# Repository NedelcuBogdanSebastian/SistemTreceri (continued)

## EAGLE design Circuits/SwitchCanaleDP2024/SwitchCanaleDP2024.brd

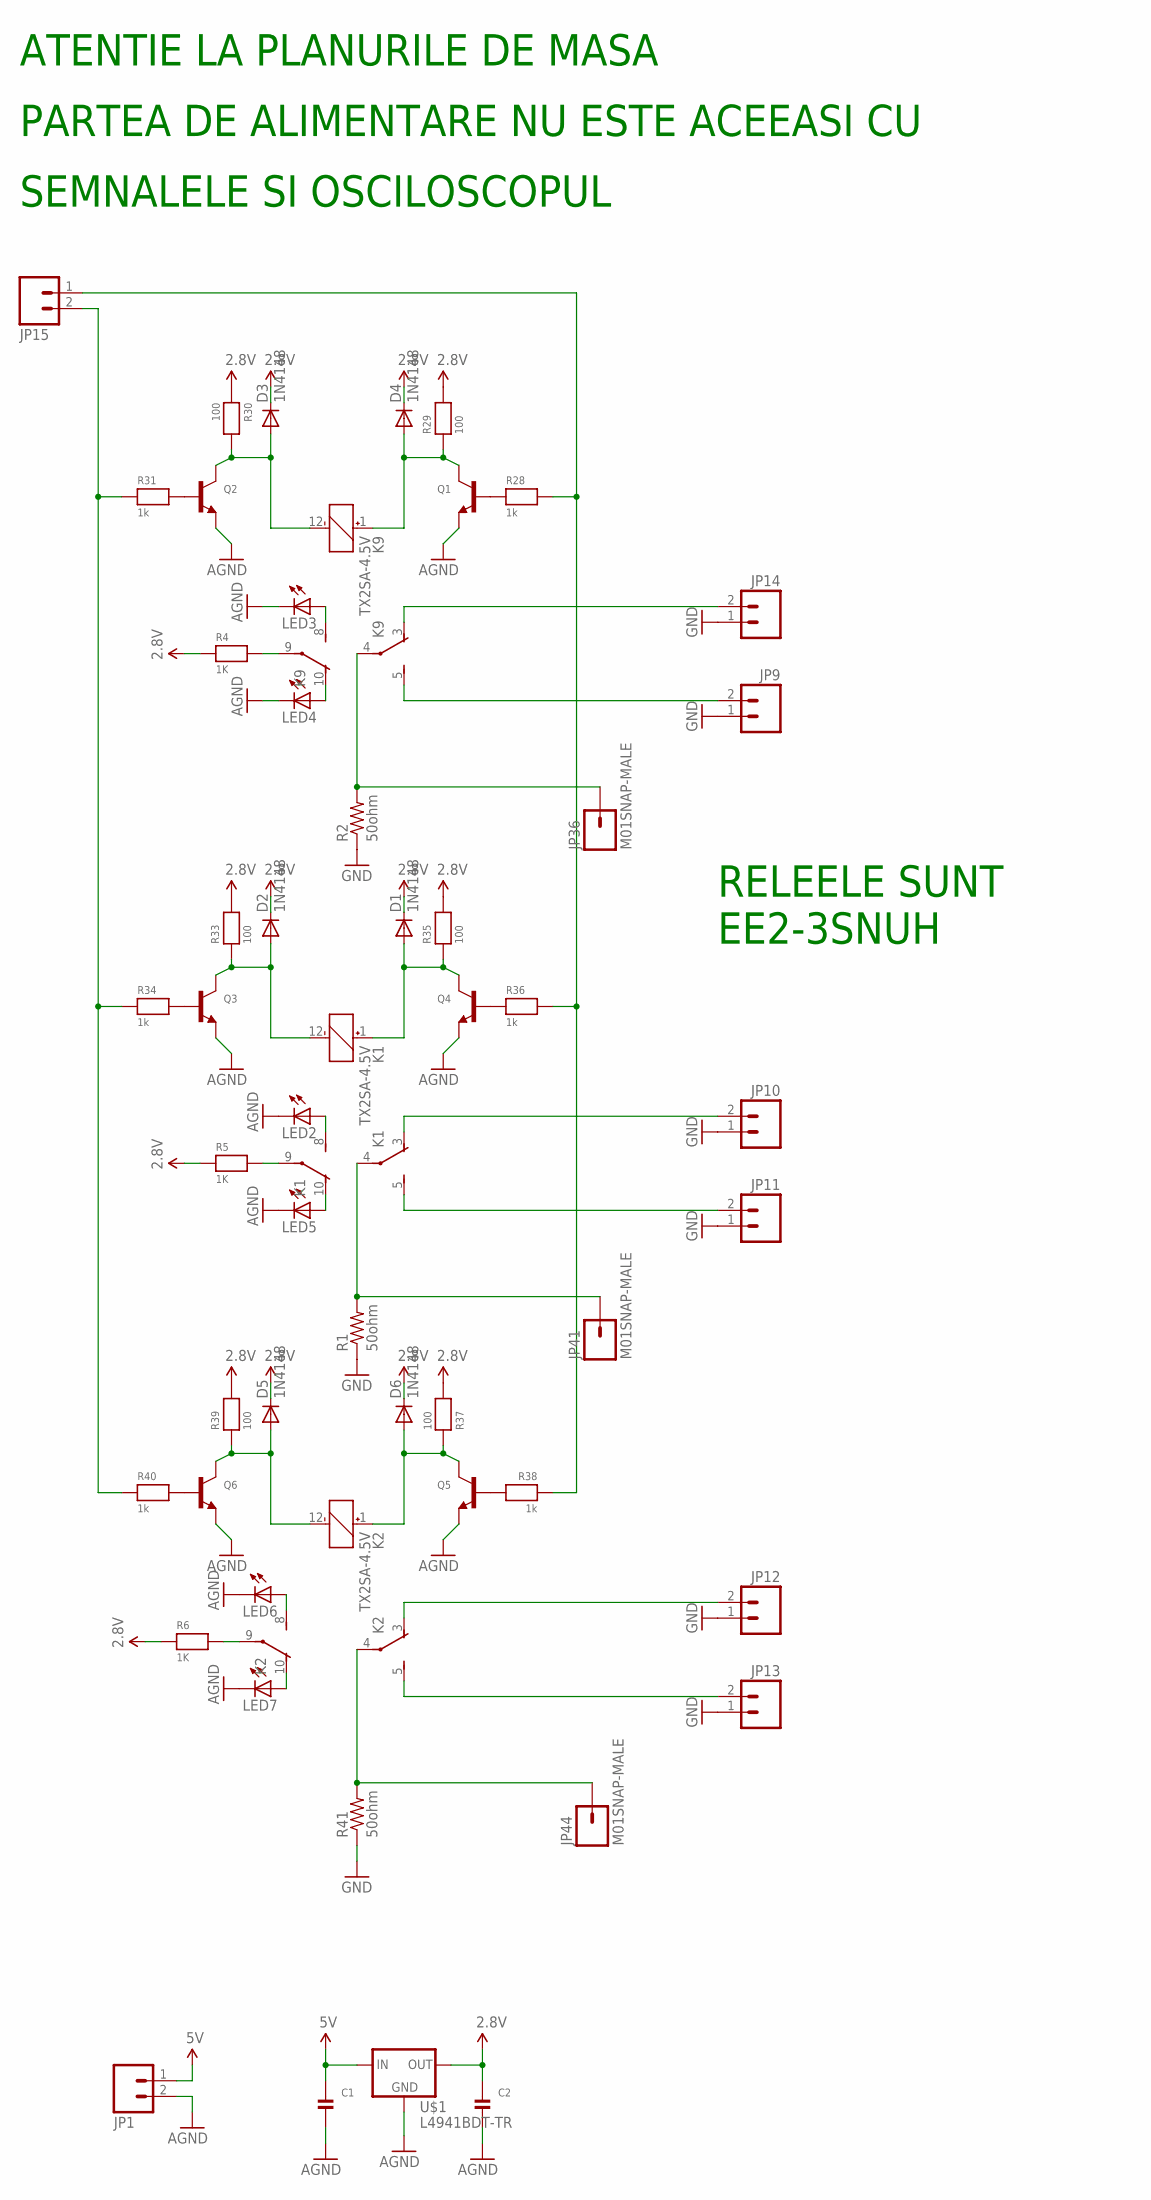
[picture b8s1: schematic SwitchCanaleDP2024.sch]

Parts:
C1, C2: CAP_CERAMIC1206; 1206
D1, D2, D3, D4, D5, D6: 1N4148; MINIMELF
JP1, JP9, JP10, JP11, JP12, JP13, JP14, JP15: M025MM; SCREWTERMINAL-5MM-2
JP36, JP41, JP44: M01SNAP-MALE; SNAP-MALE
K1, K2, K9: TX2SA-4.5V; TX2SA
LED2, LED3, LED4, LED5, LED6, LED7: LEDCHIP-LED0805; CHIP-LED0805
Q1, Q2, Q3, Q4, Q5, Q6: TRANSISTOR_NPNWAVE; SOT23-W
R1, R2, R41: 50ohm; 1206
R4, R5, R6: 1K; _0805MP
R28, R31, R34, R36, R38, R40: 1k; _0805MP
R29, R30, R33, R35, R37, R39: 100; _0805MP
U$1: L4941BDT-TR; DPAK

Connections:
2.8V: C2.1, D1.C, D2.C, D3.C, D4.C, D5.C, D6.C, R4.1, R5.1, R6.1, R29.2, R30.1, R33.2, R35.2, R37.2, R39.2, U$1.2 (OUT)
5V: C1.1, JP1.1, U$1.1 (IN)
AGND: C1.2, C2.2, JP1.2, LED2.C, LED3.C, LED4.C, LED5.C, LED6.C, LED7.C, Q1.2 (E), Q2.2 (E), Q3.2 (E), Q4.2 (E), Q5.2 (E), Q6.2 (E), U$1.3 (GND)
GND: JP9.1, JP10.1, JP11.1, JP12.1, JP13.1, JP14.1, R1.1, R2.1, R41.1
unnamed: JP15.2, R31.1, R34.1, R40.1
unnamed: D4.A, K9.1 (+), Q1.3 (C), R29.1
unnamed: K9.8 (S), LED3.A
unnamed: K9.10 (O), LED4.A
unnamed: K9.9, R4.2
unnamed: JP14.2, K9.3 (O)
unnamed: JP9.2, K9.5 (S)
unnamed: JP15.1, R28.2, R36.2, R38.1
unnamed: JP12.2, K2.3 (O)
unnamed: K1.8 (S), LED2.A
unnamed: K1.10 (O), LED5.A
unnamed: K2.8 (S), LED6.A
unnamed: K2.10 (O), LED7.A
unnamed: K2.9, R6.2
unnamed: JP36.2, K9.4, R2.2
unnamed: K1.9, R5.2
unnamed: D1.A, K1.1 (+), Q4.3 (C), R35.1
unnamed: D2.A, K1.12 (-), Q3.3 (C), R33.1
unnamed: JP10.2, K1.3 (O)
unnamed: JP11.2, K1.5 (S)
unnamed: JP41.2, K1.4, R1.2
unnamed: D6.A, K2.1 (+), Q5.3 (C), R37.1
unnamed: JP13.2, K2.5 (S)
unnamed: JP44.2, K2.4, R41.2
unnamed: Q5.1 (B), R38.2
unnamed: Q6.1 (B), R40.2
unnamed: D5.A, K2.12 (-), Q6.3 (C), R39.1
unnamed: D3.A, K9.12 (-), Q2.3 (C), R30.2
unnamed: Q2.1 (B), R31.2
unnamed: Q1.1 (B), R28.1
unnamed: Q3.1 (B), R34.2
unnamed: Q4.1 (B), R36.1

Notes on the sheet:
EE2-3SNUH
RELEELE SUNT
ATENTIE LA PLANURILE DE MASA
PARTEA DE ALIMENTARE NU ESTE ACEEASI CU
SEMNALELE SI OSCILOSCOPUL

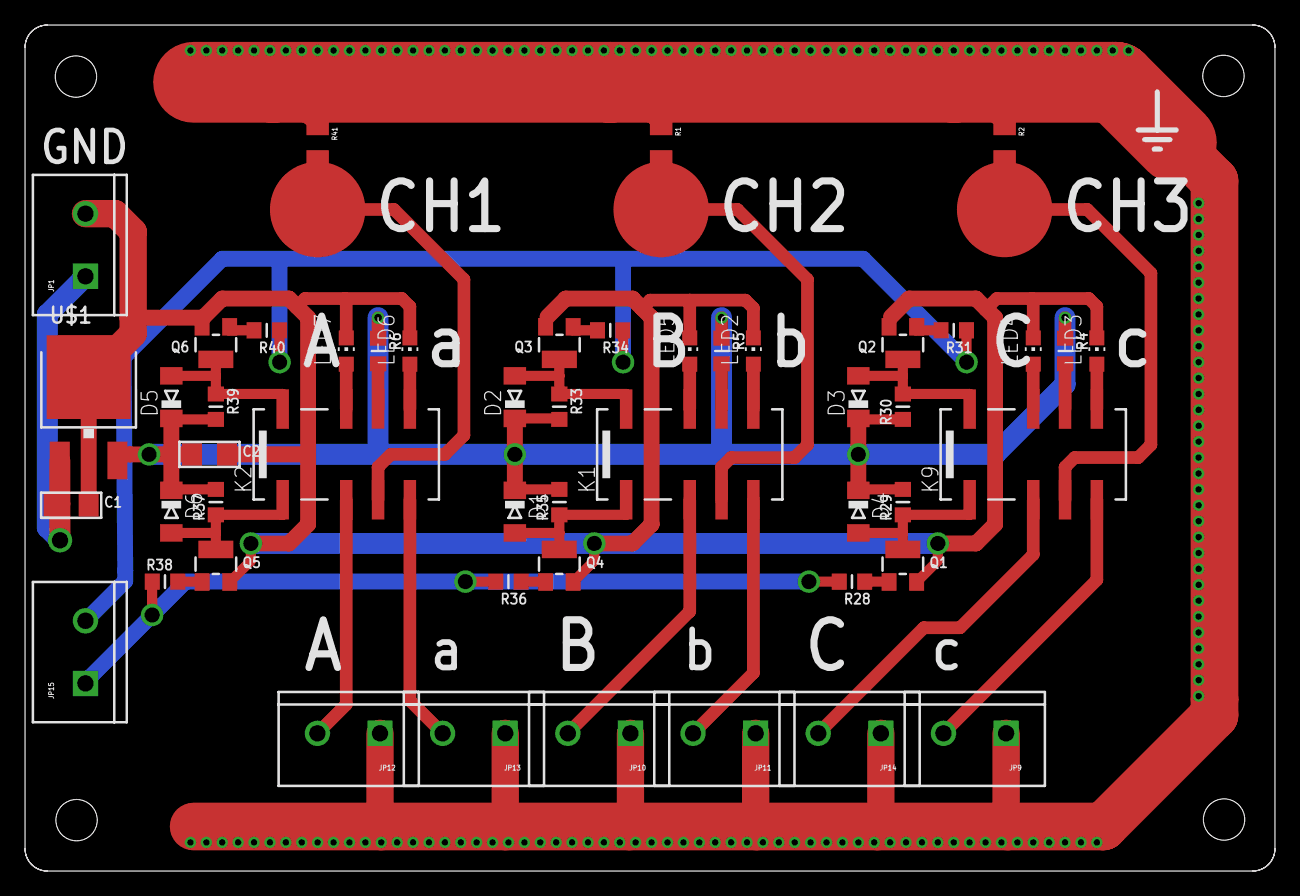
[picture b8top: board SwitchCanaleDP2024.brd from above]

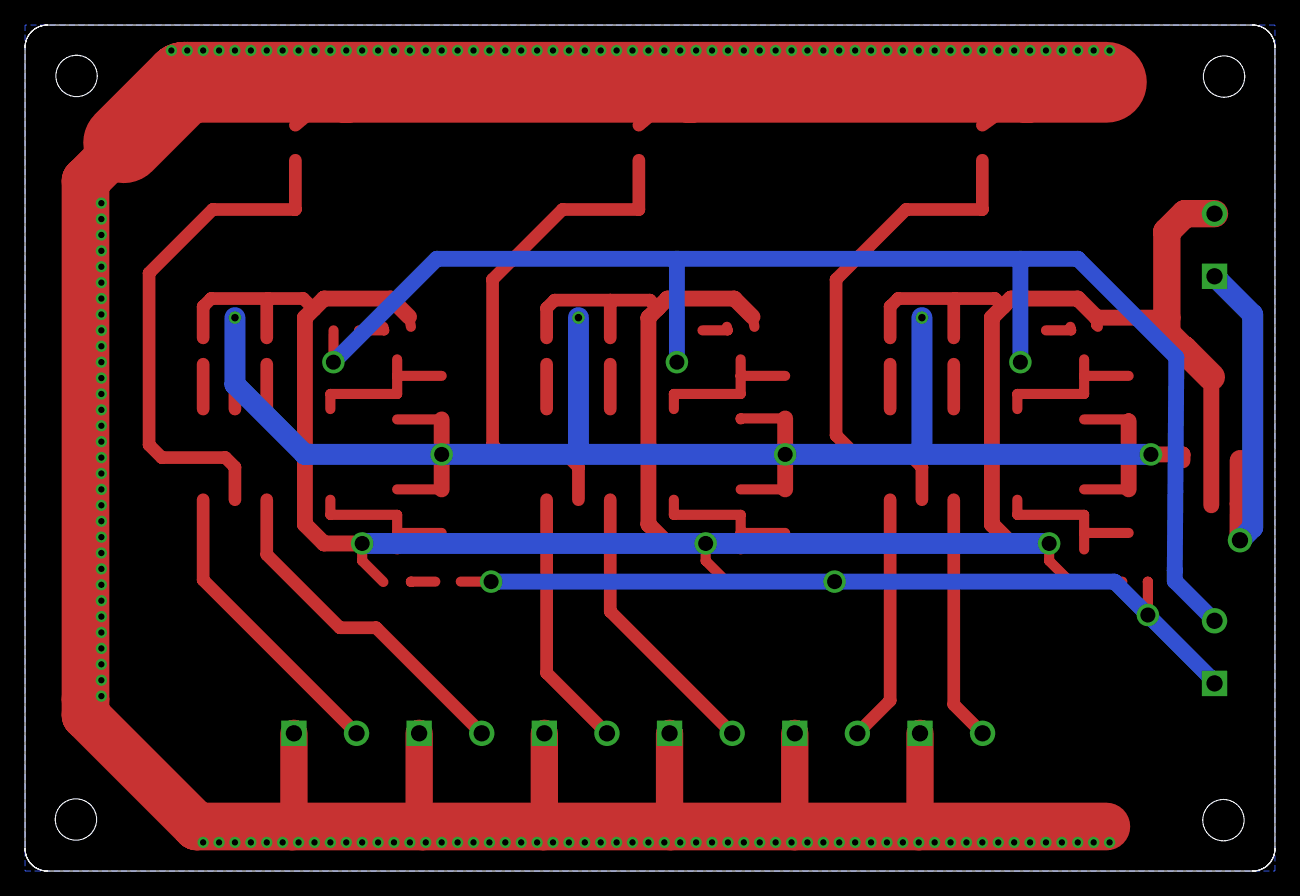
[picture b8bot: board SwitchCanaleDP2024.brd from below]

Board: 2 copper layers, 99.8 x 67.6 mm, 57 parts (4 on the bottom side), 36 nets.

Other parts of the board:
STANDOFF2, STANDOFF3, STANDOFF4, STANDOFF5: STAND-OFF

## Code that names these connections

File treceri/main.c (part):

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 *
 *    PB11 ZERO-CROSS INPUT
 *
 *    PA1 - OSC1 3MHz (TIM2_CH2) ADC
 *    PA2 - USED TO CAPTURE /DRA FROM ADC
 *
 *    PA3 - CS SRAM
 *    PA4 - SS ADC
 *    PA5 - SCK ADC/SRAM
 *    PA6 - MISO ADC/SRAM
 *    PA7 - MOSI ADC/SRAM
 *
 *    RELAYS
 *    ------
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    GPIO_Init(GPIOC, &GPIO_InitStructure);

    /************************************************************
    *   Init PB0 & PB1 side switching (A,B,C / a, b, c)
    *************************************************************/
    RCC_APB2PeriphClockCmd(RCC_APB2Periph_GPIOB , ENABLE);
    GPIO_StructInit(&GPIO_InitStructure);
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    GPIOB->BRR = GPIO_Pin_1 |GPIO_Pin_0;

    /************************************************************
    *   Init PA2 as input floating to get /DRA channel
    *************************************************************/
    RCC_APB2PeriphClockCmd(RCC_APB2Periph_GPIOA , ENABLE);
    GPIO_StructInit(&GPIO_InitStructure);
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    GPIO_Init(GPIOA, &GPIO_InitStructure);

    /************************************************************
    *   Start TIM2_CH2 on pin PA1 at 3 MHz, 50 % duty
    *   as clock for MCP3903 ADC
    *************************************************************/
    RCC_APB2PeriphClockCmd(RCC_APB2Periph_GPIOA | RCC_APB2Periph_AFIO, ENABLE);
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    TIM_OCInitStructure.TIM_OutputState = TIM_OutputState_Enable;
    TIM_OCInitStructure.TIM_Pulse = 0;
    TIM_OCInitStructure.TIM_OCPolarity = TIM_OCPolarity_High;
    TIM_OC2Init(TIM2, &TIM_OCInitStructure);  // Channel 2 configuration = PA1

    TIM_ARRPreloadConfig(TIM2, ENABLE);
    TIM_CtrlPWMOutputs(TIM2, ENABLE);
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    TIM2->CCR2 = 1;

    /************************************************************
    *   Init PB11 as input floating to get zero-cross impulse
    *************************************************************/
    RCC_APB2PeriphClockCmd(RCC_APB2Periph_GPIOB , ENABLE);
    GPIO_InitStructure.GPIO_Pin =  GPIO_Pin_11;
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
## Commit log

2024-10-07 Rename calculatePhaseFromFFT.c to calculatePhaseFromFFT_TEST_ME.c
